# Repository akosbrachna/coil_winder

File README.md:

# coil_winder

MPLAB project

The circuit consists of 

1x PIC18F2550 microcontroller, 

2x L293D motor drivers, 

1x MAX232 serial port chip, 

2x nema 17 stepper motors

One motor is winding the coil while the other one is moving a guider forth and back along the width of the core
to aid laying the wire side by side on the core.

The microcontroller receives the coil parameters on serial port from a windows program 
that provides the user interface for the circuit. https://github.com/akosbrachna/coil_winder_interface

Future plan is to add a current sensor resistor on the high voltage input that will be connected to the analog comparator 
of the microcontroller. The microcontroller through a power transistor would limit the input current on the drivers
if the current exceeds the specified current of the drivers.

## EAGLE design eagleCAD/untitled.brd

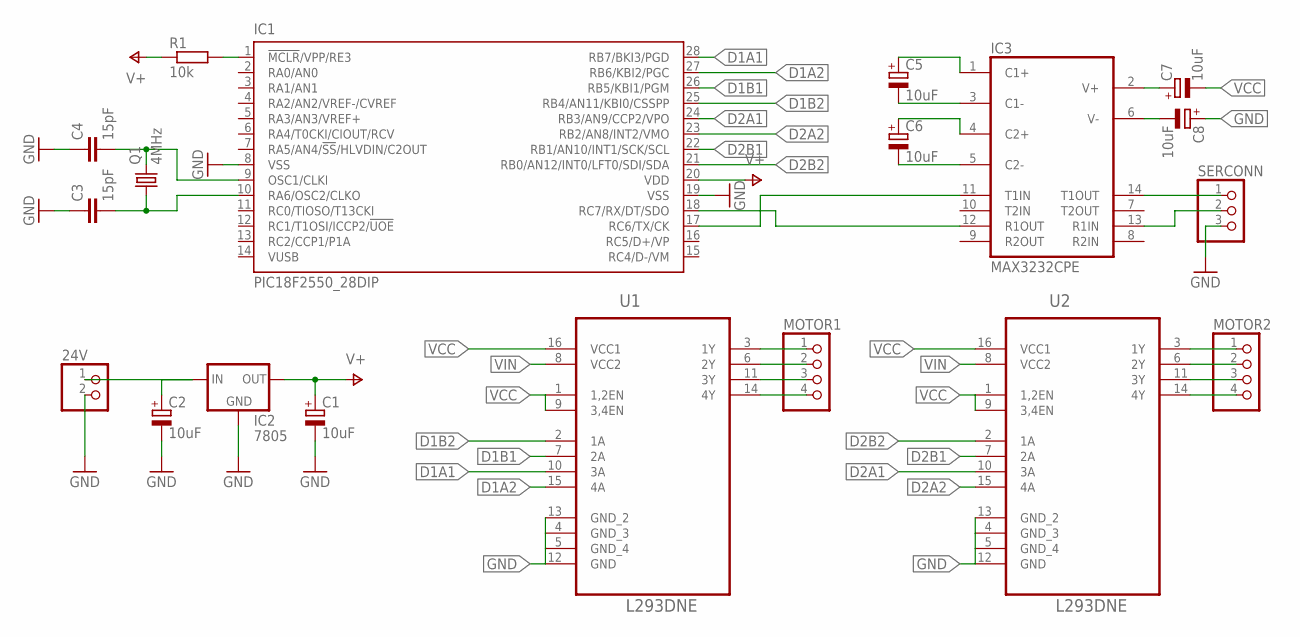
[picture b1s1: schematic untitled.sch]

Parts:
24V: PINHD-1X2; 1X02
C1, C2, C5, C6, C7, C8: 10uF; E2,5-6; MPN 100PK10MEFC5X11
C3, C4: 15pF; C7.5B6; MPN 08051A150JAT2A
IC1: PIC18F2550_28DIP; DIL28-3
IC2: 7805; 78XXL; MPN L7805ACV
IC3: MAX3232CPE; DIL16
MOTOR1, MOTOR2: PINHD-1X4; 1X04
Q1: 4MHz; HC49/S; MPN HC49US4.000MABJ-UB
R1: 10k; 0309/12; MPN CR0805-FX-1002ELF
SERCONN: PINHD-1X3; 1X03
U1, U2: L293DNE; DIP254P762X508-16

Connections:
D1A1: IC1.28 (RB7/BKI3/PGD), U1.10 (3A)
D1A2: IC1.27 (RB6/KBI2/PGC), U1.15 (4A)
D1B1: IC1.26 (RB5/KBI1/PGM), U1.7 (2A)
D1B2: IC1.25 (RB4/AN11/KBI0/CSSPP), U1.2 (1A)
D2A1: IC1.24 (RB3/AN9/CCP2/VPO), U2.10 (3A)
D2A2: IC1.23 (RB2/AN8/INT2/VMO), U2.15 (4A)
D2B1: IC1.22 (RB1/AN10/INT1/SCK/SCL), U2.7 (2A)
D2B2: IC1.21 (RB0/AN12/INT0/LFT0/SDI/SDA), U2.2 (1A)
GND: 24V.2, C1.-, C2.-, C3.1, C4.1, C8.+, IC1.8 (VSS), IC1.19 (VSS), IC2.GND, IC3.15 (GND), SERCONN.3, U1.4 (GND_3), U1.5 (GND_4), U1.12 (GND), U1.13 (GND_2), U2.4 (GND_3), U2.5 (GND_4), U2.12 (GND), U2.13 (GND_2)
unnamed: C4.2, IC1.9 (OSC1/CLKI), Q1.2
unnamed: C3.2, IC1.10 (RA6/OSC2/CLKO), Q1.1
unnamed: IC3.14 (T1OUT), SERCONN.1
unnamed: C7.+, IC3.2 (V+)
unnamed: C8.-, IC3.6 (V-)
unnamed: C5.-, IC3.3 (C1-)
unnamed: C5.+, IC3.1 (C1+)
unnamed: C6.-, IC3.5 (C2-)
unnamed: C6.+, IC3.4 (C2+)
unnamed: IC1.18 (RC7/RX/DT/SDO), IC3.12 (R1OUT)
unnamed: IC1.17 (RC6/TX/CK), IC3.11 (T1IN)
unnamed: MOTOR1.3, U1.11 (3Y)
unnamed: MOTOR1.4, U1.14 (4Y)
unnamed: MOTOR1.1, U1.3 (1Y)
unnamed: IC1.1 (!MCLR!/VPP/RE3), R1.2
unnamed: IC3.13 (R1IN), SERCONN.2
unnamed: MOTOR1.2, U1.6 (2Y)
unnamed: MOTOR2.1, U2.3 (1Y)
unnamed: MOTOR2.2, U2.6 (2Y)
unnamed: MOTOR2.3, U2.11 (3Y)
unnamed: MOTOR2.4, U2.14 (4Y)
V+: R1.1
VCC: C1.+, C7.-, IC1.20 (VDD), IC2.OUT, IC3.16 (VCC), U1.1 (1,2EN), U1.9 (3,4EN), U1.16 (VCC1), U2.1 (1,2EN), U2.9 (3,4EN), U2.16 (VCC1)
VIN: 24V.1, C2.+, IC2.IN, U1.8 (VCC2), U2.8 (VCC2)

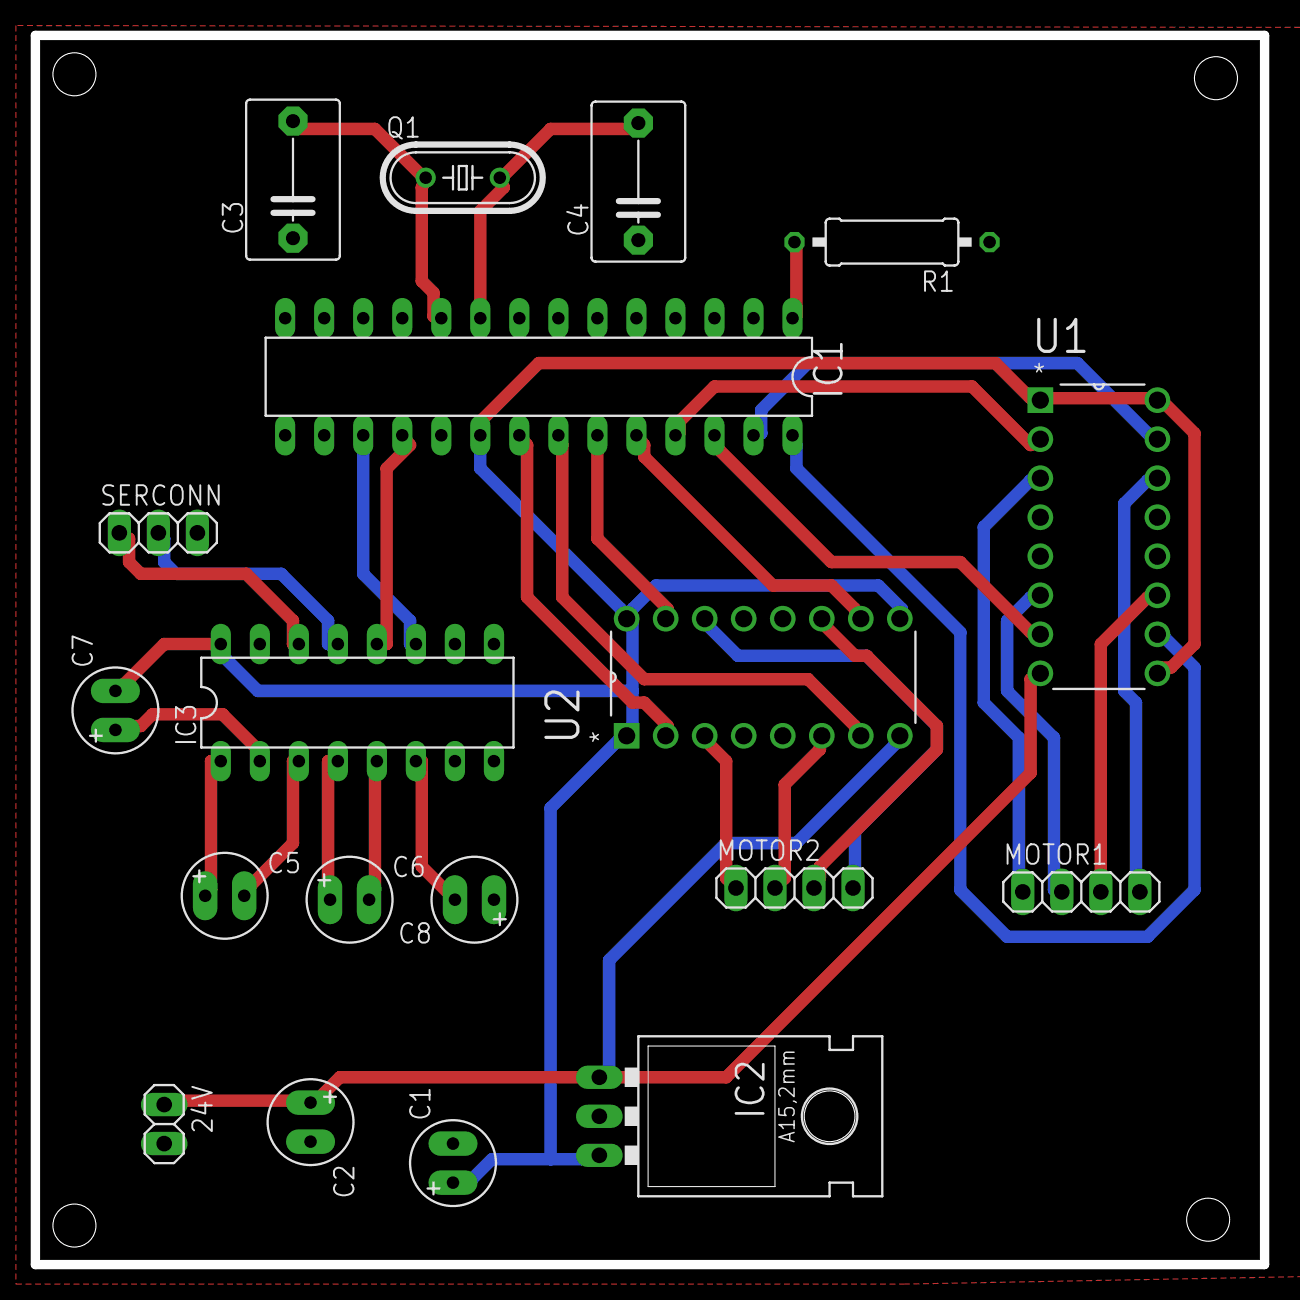
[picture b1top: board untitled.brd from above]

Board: 2 copper layers, 80.0 x 80.0 mm, 19 parts (0 on the bottom side), 32 nets.

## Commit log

2017-06-28 added circuit schematic
2017-06-28 edited readme
2017-06-28 added picture
